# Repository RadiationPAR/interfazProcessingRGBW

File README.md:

# PowerPAR-Led DELMA
---
La formulación de un problema es a menudo más esencial que su solución, que puede ser meramente una materia de destreza experimental o matemática. "La especificación del problema a investigar implica que se ha comprendido plenamente el
tema de la investigación, hasta el punto de poder determinar exactamente los interrogantes principales que plantea y a cuya resolución se debe orientar la investigación." Einstein

## SISTEMA DE MEDICIÓN Y MONITOREO PARA EL ESTUDIO DEL EFECTO DE LA RADIACIÓN PAR EN LAS PLANTAS

Esta investigación discrimina la información científica y tecnológica experimental a la fecha sobre la Radiación Fotosintéticamente Activa (radiación integrada del rango de longitudes de onda que son capaces de producir actividad fotosintética en las plantas y otros organismos fotosintéticos como microalgas y bacterias).

Investigadores de todo el planeta exponen en sus artículos que los vegetales necesitan porciones de luz desde los 400nm hasta los 700 nm; conocer sus umbrales luminicos permitirá conseguir cosechas de gran producción y alta calidad; llevar un historial de datos sobre el efecto de la longitud de onda según las horas del día y los estadios de crecimiento de la planta permitirá a futuro disponer de hojas de datos para realizar agricultura de precisión en su parametro luminico. 

A continuación se plantea el desarrollo de un mecanismo de observación para la respuesta fisiológica del dosel vegetal (en especial de la fotosíntesis), a partir del diseño de un sistema de iluminación artificial basado en un estudio previo de sistemas de iluminación y la actual migración a sistemas de iluminación con tecnología LED y OLED cuyo espectro de radiación esta dado en una banda especifica lo que proporciona un menor gasto de potencia, y facilita irradiar la planta con la parte del espectro especifico que ella necesita según su estadio: germinación, vegetación y floración. 

Fabricantes de todo el mundo, ofrecen al mercado diversas lamparas de iluminación y en algunos casos se diseñan enormes arreglos de leds con iluminación fija o invariable garantizando solo su uso para determinado tipo de plantas (C3, C4, CAM) - plantas presentes en la industria hortícola de mayor producción. Los investigadores de diversas tesis de Maestría y Doctorado no realizan un proceso fiable para llevar la trazabilidad de sus datos pero nos ilustran sobre el metodo científico iterado para obtener mejoras en el proceso de crecimiento y floración de diversas genéticas de plantas.  

Esta investigación contempla el desarrollo de un prototipo que permite al usuario manejar: la composición de color (longitud de onda) a irradiar y su potencia a traves de una interfaz de fácil manejo que almacena datos de manera centralizada como lo son: composición RGB (0-255), composición CMY (0 - 255), Matiz (0 - 360), saturación (0.0 - 1.0), luminancia (0.0 - 1.0), posición XYZ del color, longitud de onda y frecuencia.   

# Materiales
---  
## Microcontrolador Tiva C Series  
Se decide implementar este microcontrolador por su fama en internet acerca de la adquisición, procesamiento y almacenamiento de datos; ademas se sirve de una librería para la compresión de algoritmos matemáticos, lo cual resulta bastante interesante y acorde para las conversiones de los diferentes modelos matemáticos de los espacios del color.

## Sensor TCS3220 y Led RGB 100W
Se opta por implementar el sensor TCS3220 por su resolución y economía; basicamente entrega una señal cuadrada con ancho de pulso variable de acuerdo a la presencia de una fuente de luz. Se caracteriza el comportamiento del sensor con la hoja de datos del fabricante y datos de pruebas en el laboratorio de ensayos eléctricos de la Universidad Nacional - LABE.  

El led de 100W permite dimensionar espacios de manera modular y cumple con los requisitos mínimos de lumenes para estimular la fotosíntesis en plantas C3, C4 y CAM.

# Diseño esquematico y PCB 
---  
## Circuito de Potencia

## Circuito de Control

---  

# Interfaz de Control con Processing desde una Raspberry

Para el desarrollo de la interfaz se usa el software libre Processing - ampliamente usado para comunicación entre el usuario y la maquina por el protocolo RS-232 haciendo el llamado de la libreria "ControlP5".  
Para configurarle en una **raspberry** deben ejecutarse los siguientes comandos: 
<pre><code>cd interfazProcessingRGBW/PROCESSING/controlP5-2.2.5/controlP5/library</code></pre>
<pre><code>cp controlP5.jar /usr/local/lib/processing-3.2.3/core/library</code></pre>  
---

## Investigador principal
* Diego Javier Mena - Email: ingelectronicadj@gmail.com

## Apoyo a la investigación

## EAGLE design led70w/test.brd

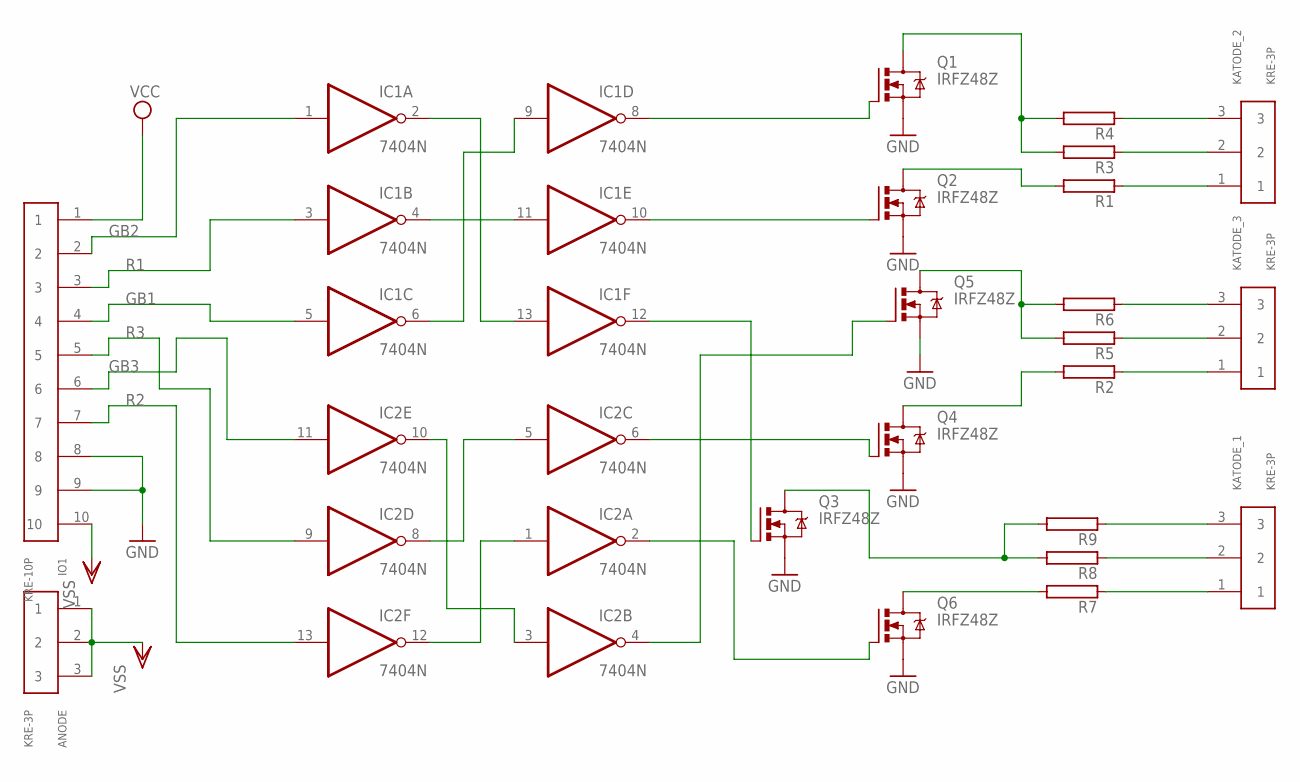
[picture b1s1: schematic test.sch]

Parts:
ANODE: KRE-3P
IC1, IC2: 7404N; DIL14
IO1: KRE-10P
KATODE_1, KATODE_2, KATODE_3: KRE-3P
Q1, Q2, Q3, Q4, Q5, Q6: IRFZ48Z; TO220BH
R1, R2, R3, R4, R5, R6, R7, R8, R9: RAC10; AC10

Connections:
GB1: IC1.5 (I), IO1.4
GB2: IC1.1 (I), IO1.2
GB3: IC2.11 (I), IO1.6
GND: IC1.7 (GND), IC2.7 (GND), IO1.8, IO1.9, Q1.S, Q2.S, Q3.S, Q4.S, Q5.S, Q6.S
K_B: Q2.D, R1.2
K_B2: Q5.D, R5.2, R6.2
K_R: Q1.D, R3.2, R4.2
unnamed: IC1.8 (O), Q1.G
unnamed: IC1.10 (O), Q2.G
unnamed: KATODE_2.1, R1.1
unnamed: IC1.12 (O), Q3.G
unnamed: IC1.4 (O), IC1.11 (I)
unnamed: IC2.1 (I), IC2.12 (O)
unnamed: IC2.5 (I), IC2.8 (O)
unnamed: IC2.6 (O), Q4.G
unnamed: IC2.2 (O), Q6.G
unnamed: IC2.4 (O), Q5.G
unnamed: IC2.3 (I), IC2.10 (O)
unnamed: IC1.6 (O), IC1.9 (I)
unnamed: KATODE_2.2, R3.1
unnamed: KATODE_2.3, R4.1
unnamed: IC1.2 (O), IC1.13 (I)
unnamed: KATODE_3.1, R2.1
unnamed: KATODE_3.2, R5.1
unnamed: KATODE_3.3, R6.1
unnamed: KATODE_1.1, R7.1
unnamed: KATODE_1.2, R8.1
unnamed: KATODE_1.3, R9.1
unnamed: Q3.D, R8.2, R9.2
unnamed: Q6.D, R7.2
unnamed: Q4.D, R2.2
R1: IC1.3 (I), IO1.3
R2: IC2.13 (I), IO1.7
R3: IC2.9 (I), IO1.5
VCC: IC1.14 (VCC), IC2.14 (VCC), IO1.1
VSS: ANODE.1, ANODE.2, ANODE.3, IO1.10

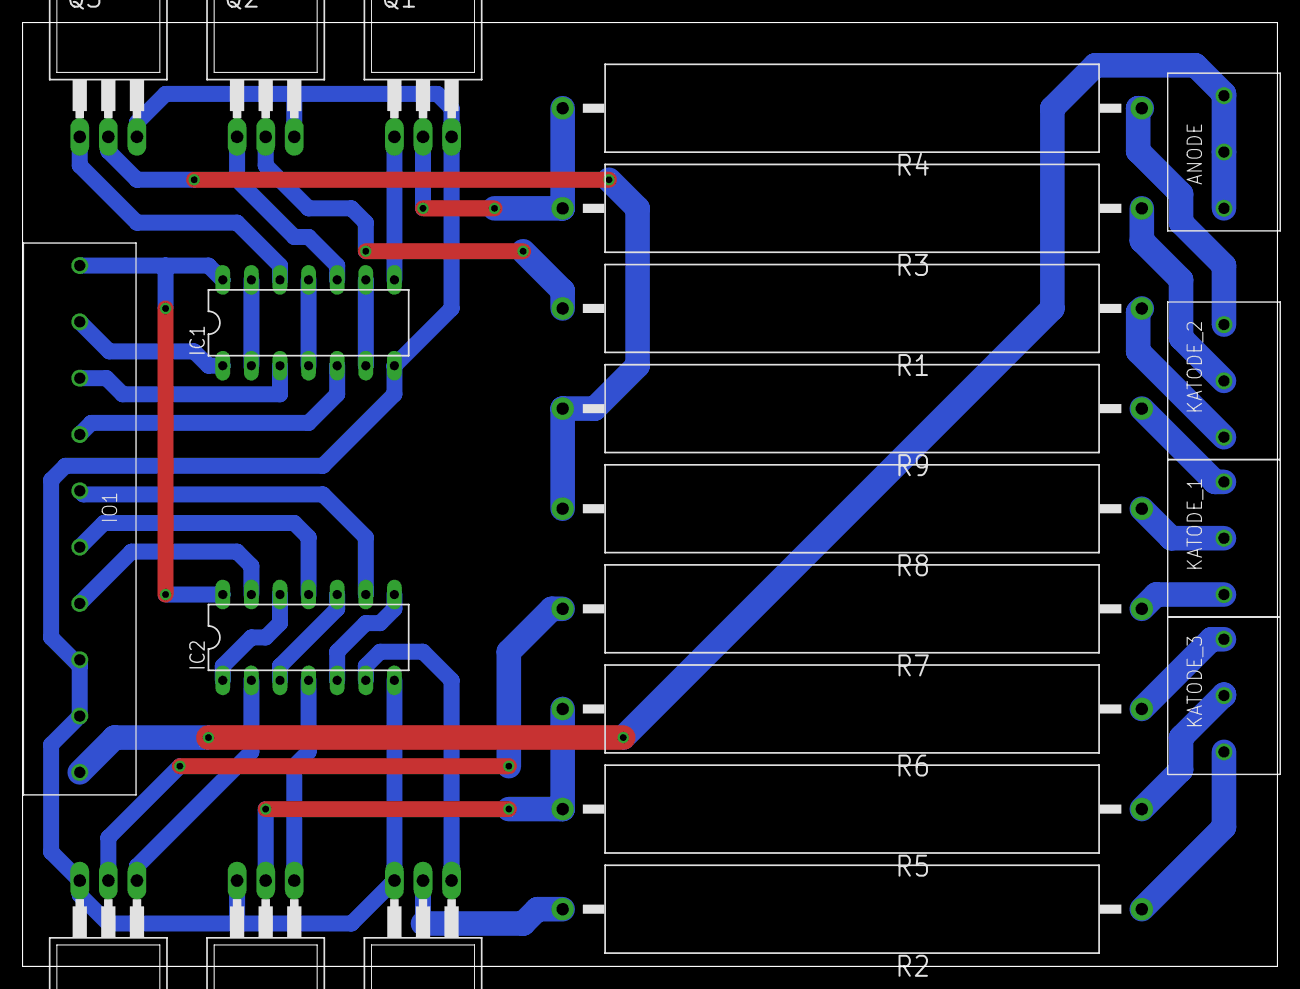
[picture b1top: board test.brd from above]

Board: 2 copper layers, 111.4 x 83.8 mm, 22 parts (0 on the bottom side), 36 nets.

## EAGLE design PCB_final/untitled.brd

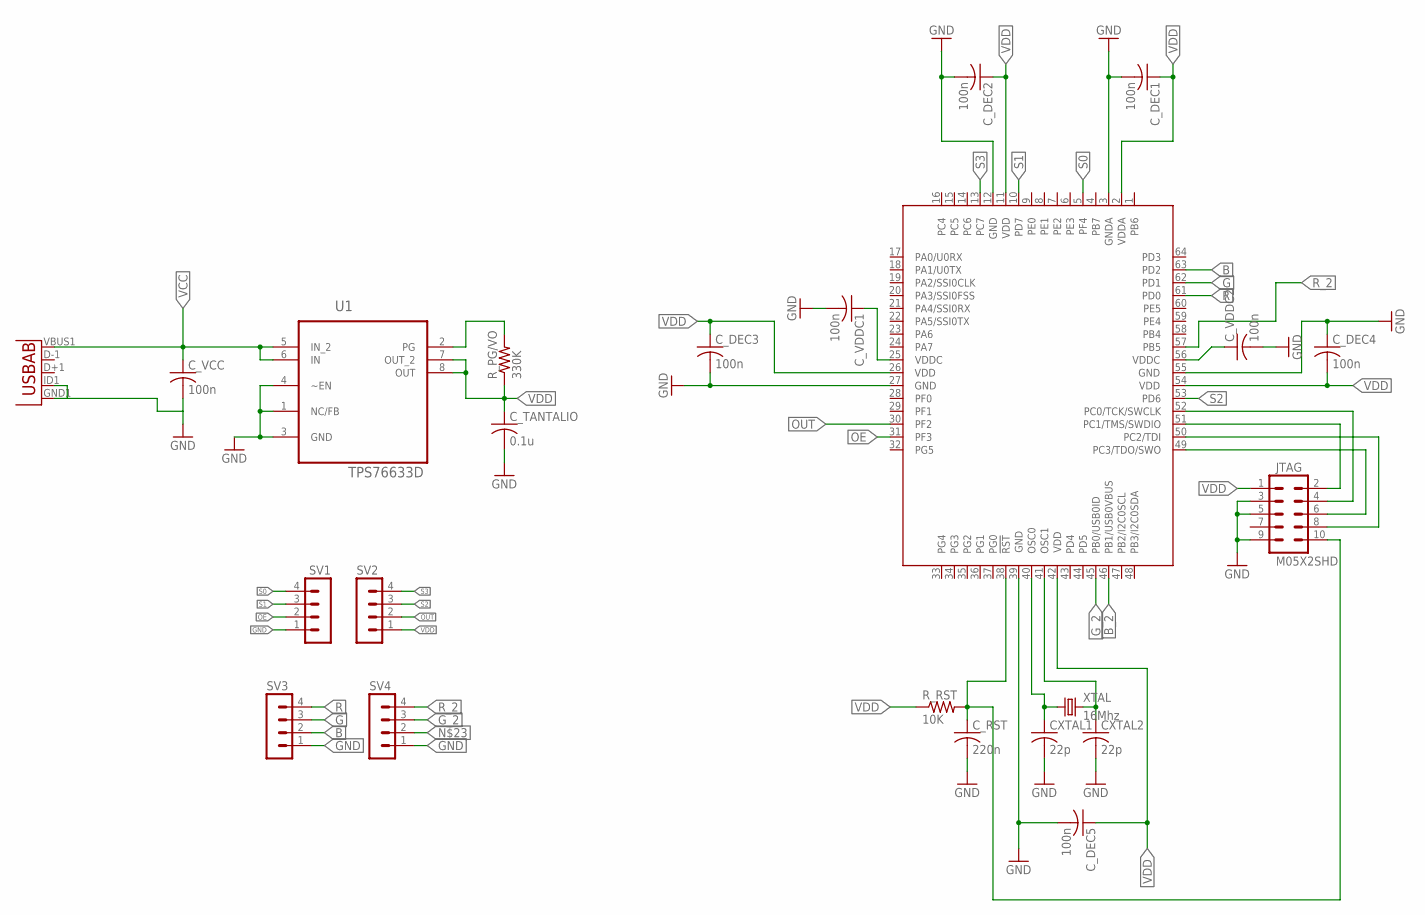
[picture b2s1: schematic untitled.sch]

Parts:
CXTAL1, CXTAL2: 22p; C0805
C_DEC1, C_DEC2, C_DEC3, C_DEC4, C_DEC5: 100n; C0805
C_RST: 220n; C0805
C_TANTALIO: 0.1u; C1206
C_VCC: 100n; C0805
C_VDDC1, C_VDDC2: 100n; C0805
JTAG: M05X2SHD; 2X5-SHROUDED
R_PG/VO: 330K; M1206
R_RST: 10K; M1206
SV1, SV2, SV3, SV4: MA04-1
TM4C123FH6PM: TM4C123[6,F]XXPM; PM_S-PQFP-G64
U1: TPS76633D; SOIC127P600X175-8N
U3: USB""; USB-MICRO-SMD
XTAL: 16Mhz; HC49UP

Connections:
B: SV3.2, TM4C123FH6PM.63 (PD2)
B_2: TM4C123FH6PM.46 (PB1/USB0VBUS)
G: SV3.3, TM4C123FH6PM.62 (PD1)
GND: CXTAL1.2, CXTAL2.2, C_DEC1.2, C_DEC2.2, C_DEC3.2, C_DEC4.1, C_DEC5.2, C_RST.2, C_TANTALIO.2, C_VCC.2, C_VDDC1.2, C_VDDC2.2, JTAG.3, JTAG.5, JTAG.9, SV1.1, SV3.1, SV4.1, TM4C123FH6PM.3 (GNDA), TM4C123FH6PM.12 (GND), TM4C123FH6PM.27 (GND), TM4C123FH6PM.39 (GND), TM4C123FH6PM.55 (GND), U1.1 (NC/FB), U1.3 (GND), U1.4 (~EN), U3.GND1 (GND), U3.ID1 (USBID)
G_2: SV4.3, TM4C123FH6PM.45 (PB0/USB0ID)
unnamed: CXTAL1.1, TM4C123FH6PM.40 (OSC0), XTAL.1
unnamed: CXTAL2.1, TM4C123FH6PM.41 (OSC1), XTAL.2
unnamed: C_VDDC1.1, TM4C123FH6PM.25 (VDDC)
unnamed: JTAG.2, TM4C123FH6PM.51 (PC1/TMS/SWDIO)
unnamed: JTAG.4, TM4C123FH6PM.52 (PC0/TCK/SWCLK)
unnamed: C_VDDC2.1, TM4C123FH6PM.56 (VDDC)
unnamed: JTAG.6, TM4C123FH6PM.49 (PC3/TDO/SWO)
unnamed: R_PG/VO.2, U1.2 (PG)
unnamed: JTAG.8, TM4C123FH6PM.50 (PC2/TDI)
unnamed: C_RST.1, JTAG.10, R_RST.2, TM4C123FH6PM.38 (!RST)
OE: SV1.2, TM4C123FH6PM.31 (PF3)
OUT: SV2.2, TM4C123FH6PM.30 (PF2)
R: SV3.4, TM4C123FH6PM.61 (PD0)
R_2: SV4.4, TM4C123FH6PM.57 (PB5)
S0: SV1.4, TM4C123FH6PM.5 (PF4)
S1: SV1.3, TM4C123FH6PM.10 (PD7)
S2: SV2.3, TM4C123FH6PM.53 (PD6)
S3: SV2.4, TM4C123FH6PM.13 (PC7)
VCC: C_VCC.1, U1.5 (IN_2), U1.6 (IN), U3.VBUS1 (VBUS)
VDD: C_DEC1.1, C_DEC2.1, C_DEC3.1, C_DEC4.2, C_DEC5.1, C_TANTALIO.1, JTAG.1, R_PG/VO.1, R_RST.1, SV2.1, TM4C123FH6PM.2 (VDDA), TM4C123FH6PM.11 (VDD), TM4C123FH6PM.26 (VDD), TM4C123FH6PM.42 (VDD), TM4C123FH6PM.54 (VDD), U1.7 (OUT_2), U1.8 (OUT)

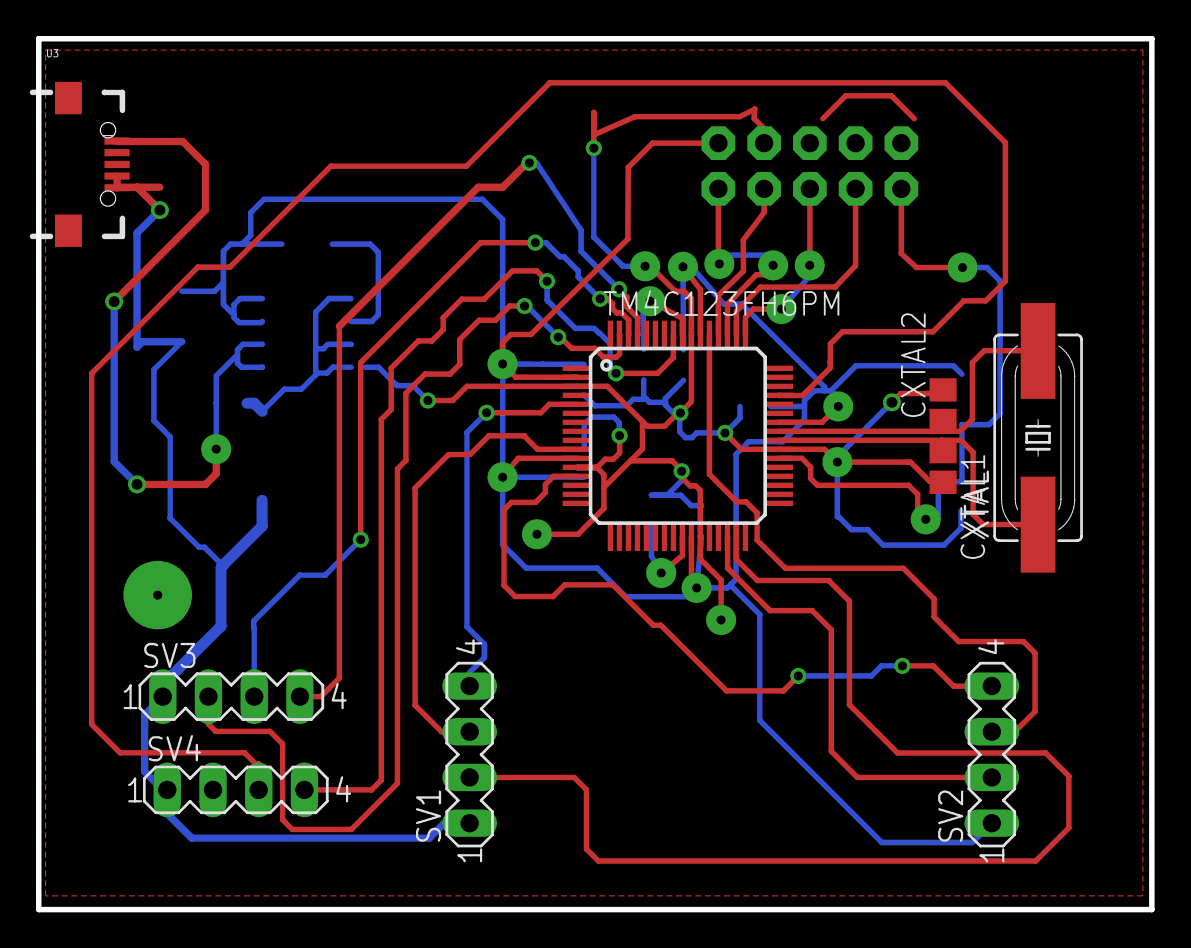
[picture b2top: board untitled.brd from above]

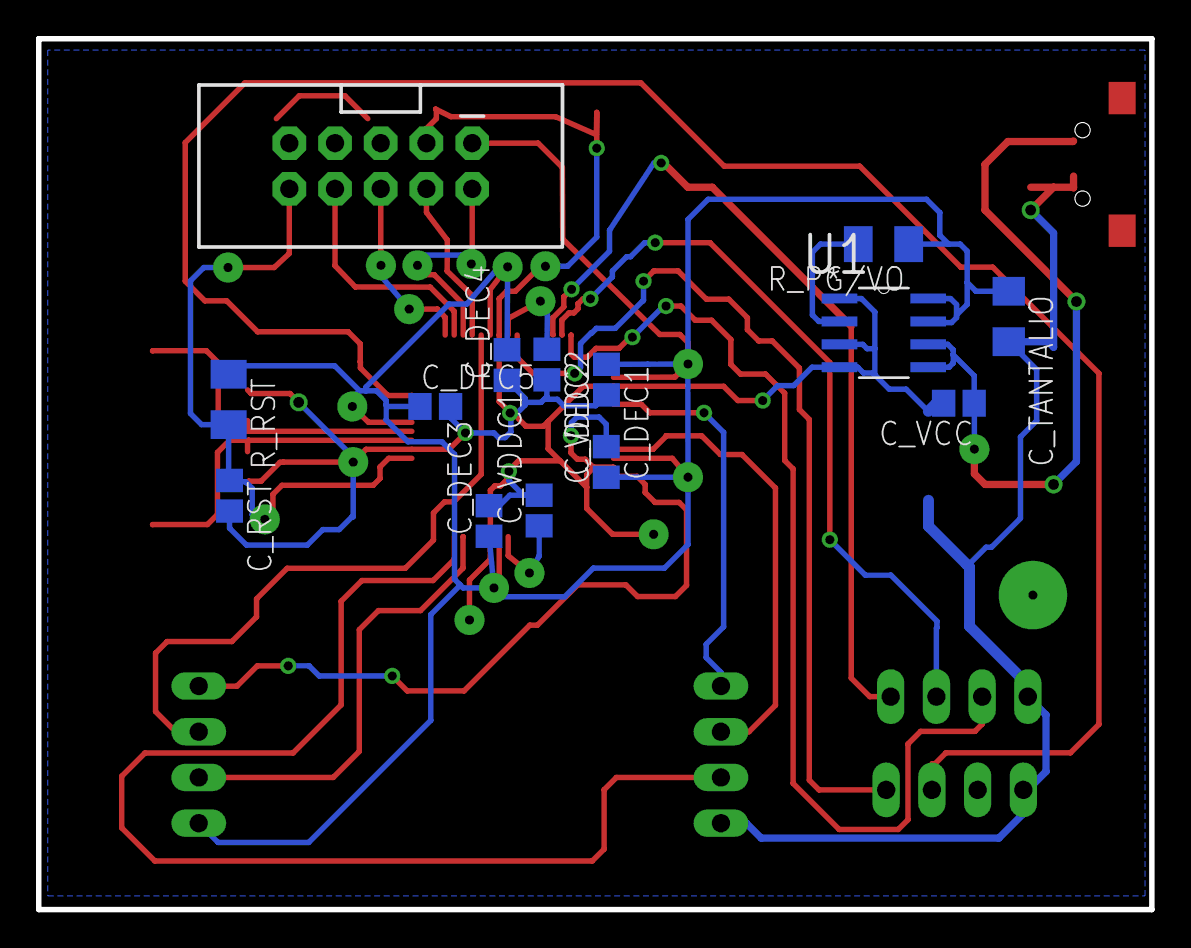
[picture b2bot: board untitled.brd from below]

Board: 2 copper layers, 61.8 x 48.4 mm, 23 parts (14 on the bottom side), 24 nets.

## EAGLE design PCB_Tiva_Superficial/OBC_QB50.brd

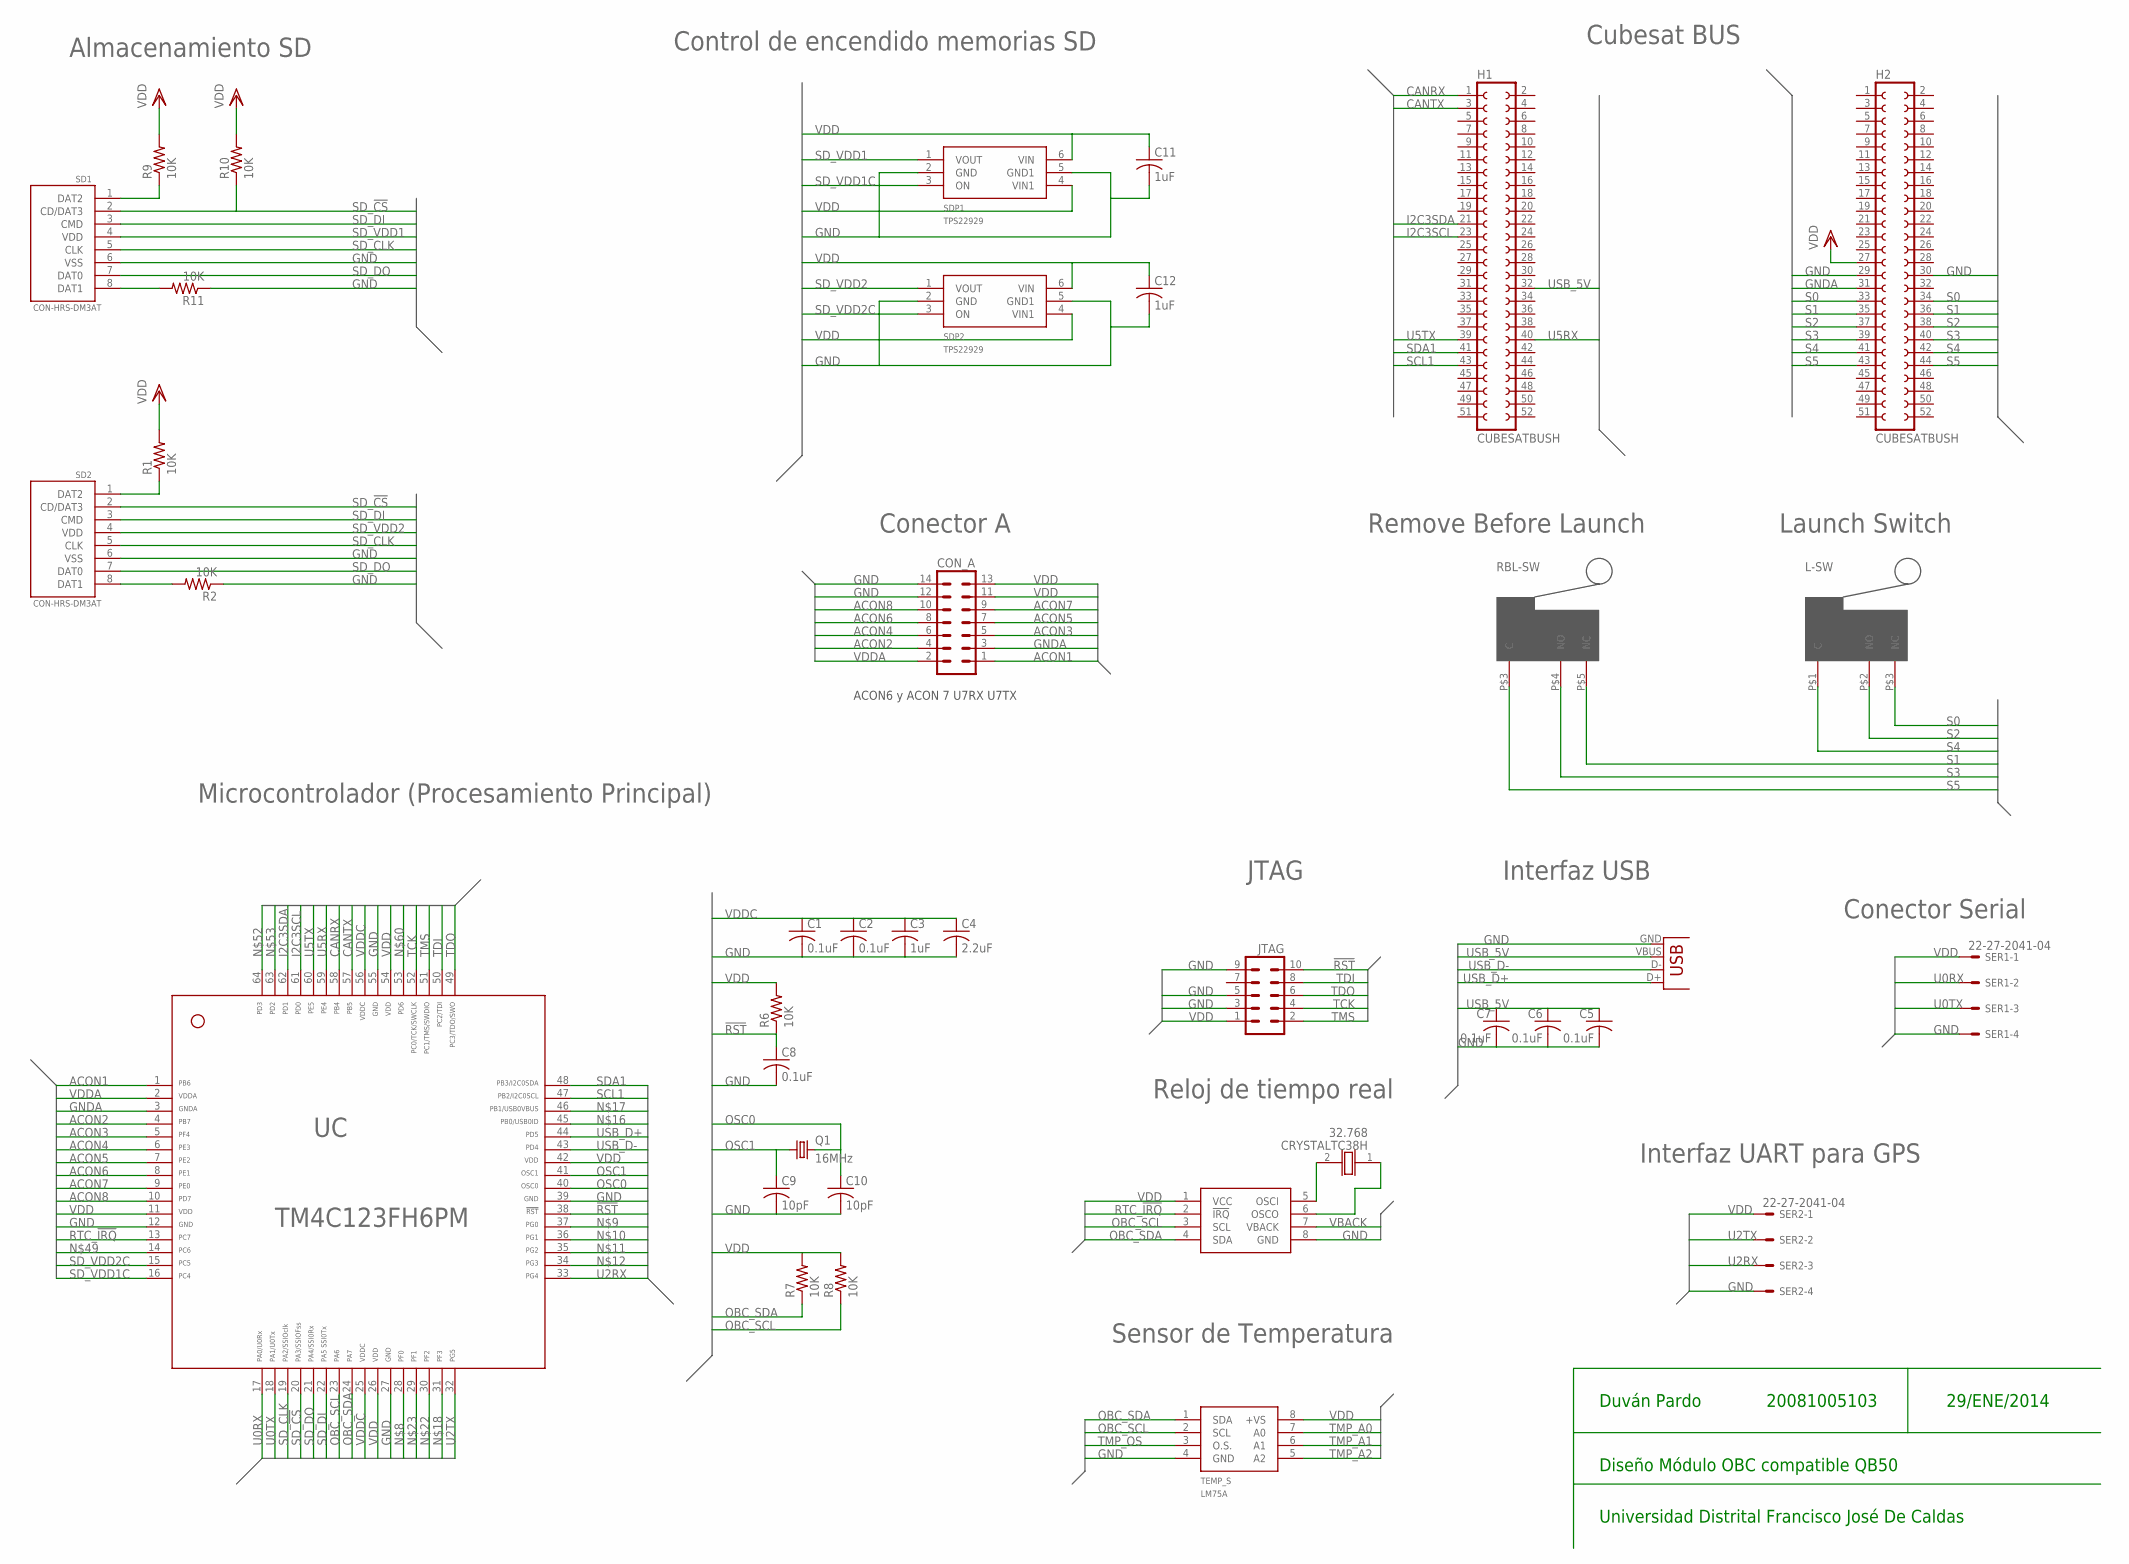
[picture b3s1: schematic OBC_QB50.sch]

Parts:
32.768: CRYSTALTC38H; TC38H
C1, C2, C5, C6, C7, C8: 0.1uF; C0402
C3, C11, C12: 1uF; C0402
C4: 2.2uF; C0402
C9, C10: 10pF; C0402
CON_A: ML14
H1, H2: CUBESATBUSH; CUBESATBUS
JTAG: ML10
L-SW: SW_E61-SERIESCON; CON
Q1: 16MHz; HC49UP
R1, R2, R6, R7, R8, R9, R10, R11: 10K; MINI_MELF-0102R
RBL-SW: SW_E61-SERIES; E61-SERIES
RTC: BQ32008SOIC; SOP08
SD1, SD2: CON-HRS-DM3AT; HRS-DM3AT
SDP1, SDP2: TPS22929; SOT23-6L
SER1, SER2: 22-27-2041-04; 6410-04
TEMP_S: LM75A; SOP08
UC: TM4C123FH6PM
USB: USB-B-H

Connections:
!RST: C8.1, JTAG.10, R6.1, UC.38
ACON1: CON_A.1, UC.1
ACON2: CON_A.4, UC.4
ACON3: CON_A.5, UC.5
ACON4: CON_A.6, UC.6
ACON5: CON_A.7, UC.7
ACON6: CON_A.8, UC.8
ACON7: CON_A.9, UC.9
ACON8: CON_A.10, UC.10
CANRX: H1.1, UC.58
CANTX: H1.3, UC.57
GND: C1.2, C2.2, C3.2, C4.2, C5.2, C6.2, C7.2, C8.2, C9.2, C10.2, C11.2, C12.2, CON_A.12, CON_A.14, H2.29, H2.30, JTAG.3, JTAG.5, JTAG.9, R2.1, R11.1, RTC.8 (GND), SD1.6 (VSS), SD2.6 (VSS), SDP1.2 (GND), SDP1.5 (GND1), SDP2.2 (GND), SDP2.5 (GND1), SER1.4, SER2.4, TEMP_S.4 (GND), UC.12, UC.27, UC.39, UC.55, USB.GND
GNDA: CON_A.3, H2.31, UC.3
I2C3SCL: H1.23, UC.61
I2C3SDA: H1.21, UC.62
unnamed: R1.1, SD2.1 (DAT2)
unnamed: R2.2, SD2.8 (DAT1)
unnamed: 32.768.2 (X2), RTC.5 (OSCI)
unnamed: 32.768.1 (X1), RTC.6 (OSCO)
unnamed: R9.1, SD1.1 (DAT2)
unnamed: R11.2, SD1.8 (DAT1)
OBC_SCL: R8.1, RTC.3 (SCL), TEMP_S.2 (SCL), UC.23
OBC_SDA: R7.1, RTC.4 (SDA), TEMP_S.1 (SDA), UC.24
OSC0: C10.1, Q1.2, UC.40
OSC1: C9.1, Q1.1, UC.41
RTC_!IRQ: RTC.2 (!IRQ), UC.13
S0: H2.33, H2.34, L-SW.P$3 (NC)
S1: H2.35, H2.36, RBL-SW.P$5 (NC)
S2: H2.37, H2.38, L-SW.P$2 (NO)
S3: H2.39, H2.40, RBL-SW.P$4 (NO)
S4: H2.41, H2.42, L-SW.P$1 (C)
S5: H2.43, H2.44, RBL-SW.P$3 (C)
SCL1: H1.43, UC.47
SDA1: H1.41, UC.48
SD_!CS: R10.1, SD1.2 (CD/DAT3), SD2.2 (CD/DAT3), UC.20
SD_CLK: SD1.5 (CLK), SD2.5 (CLK), UC.19
SD_DI: SD1.3 (CMD), SD2.3 (CMD), UC.22
SD_DO: SD1.7 (DAT0), SD2.7 (DAT0), UC.21
SD_VDD1: SD1.4 (VDD), SDP1.1 (VOUT)
SD_VDD1C: SDP1.3 (ON), UC.16
SD_VDD2: SD2.4 (VDD), SDP2.1 (VOUT)
SD_VDD2C: SDP2.3 (ON), UC.15
TCK: JTAG.4, UC.52
TDI: JTAG.8, UC.50
TDO: JTAG.6, UC.49
TMP_A0: TEMP_S.7 (A0)
TMP_A1: TEMP_S.6 (A1)
TMP_A2: TEMP_S.5 (A2)
TMP_OS: TEMP_S.3 (O.S.)
TMS: JTAG.2, UC.51
U0RX: SER1.2, UC.17
U0TX: SER1.3, UC.18
U2RX: SER2.3, UC.33
U2TX: SER2.2, UC.32
U5RX: H1.40, UC.59
U5TX: H1.39, UC.60
USB_5V: C5.1, C6.1, C7.1, H1.32, USB.VBUS
USB_D+: UC.44, USB.D+
USB_D-: UC.43, USB.D-
VBACK: RTC.7 (VBACK)
VDD: C11.1, C12.1, CON_A.11, CON_A.13, H2.27, JTAG.1, R1.2, R6.2, R7.2, R8.2, R9.2, R10.2, RTC.1 (VCC), SDP1.4 (VIN1), SDP1.6 (VIN), SDP2.4 (VIN1), SDP2.6 (VIN), SER1.1, SER2.1, TEMP_S.8 (+VS), UC.11, UC.26, UC.42, UC.54
VDDA: CON_A.2, UC.2
VDDC: C1.1, C2.1, C3.1, C4.1, UC.25, UC.56

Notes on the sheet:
Almacenamiento SD
Cubesat BUS
JTAG
Microcontrolador (Procesamiento Principal)
Interfaz USB
Remove Before Launch
Launch Switch
Reloj de tiempo real
Control de encendido memorias SD
Conector A
Conector Serial
Duván Pardo
Universidad Distrital Francisco José De Caldas
Diseño Módulo OBC compatible QB50
29/ENE/2014
20081005103
Sensor de Temperatura
ACON6 y ACON 7 U7RX U7TX
Interfaz UART para GPS

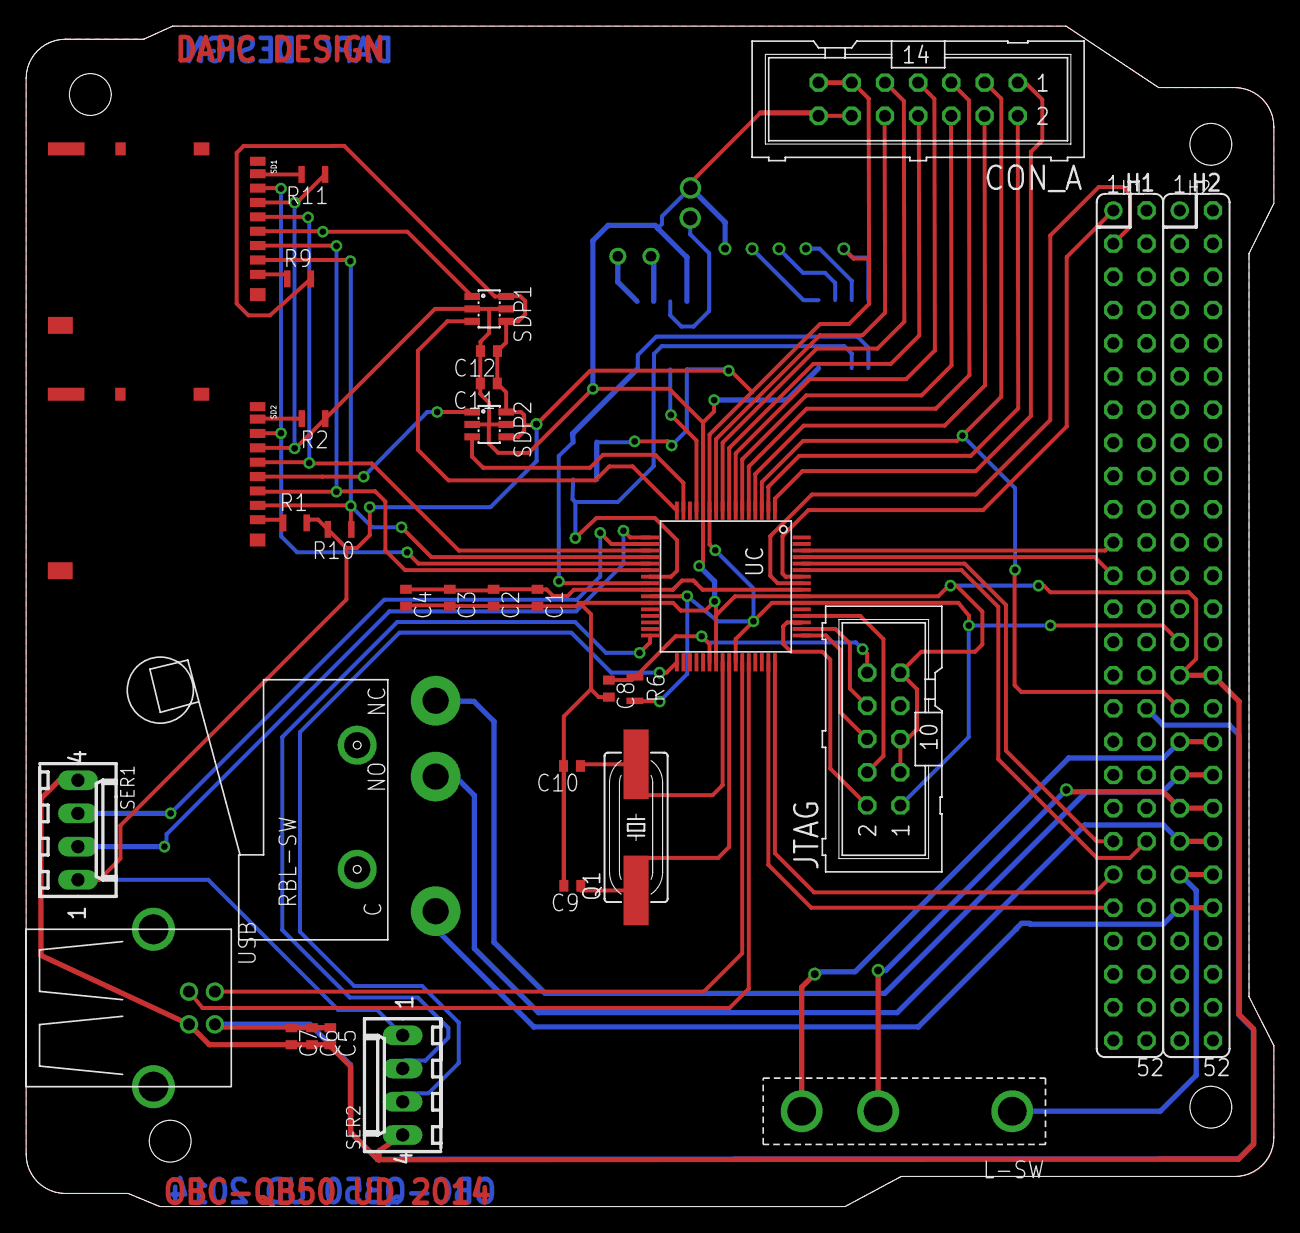
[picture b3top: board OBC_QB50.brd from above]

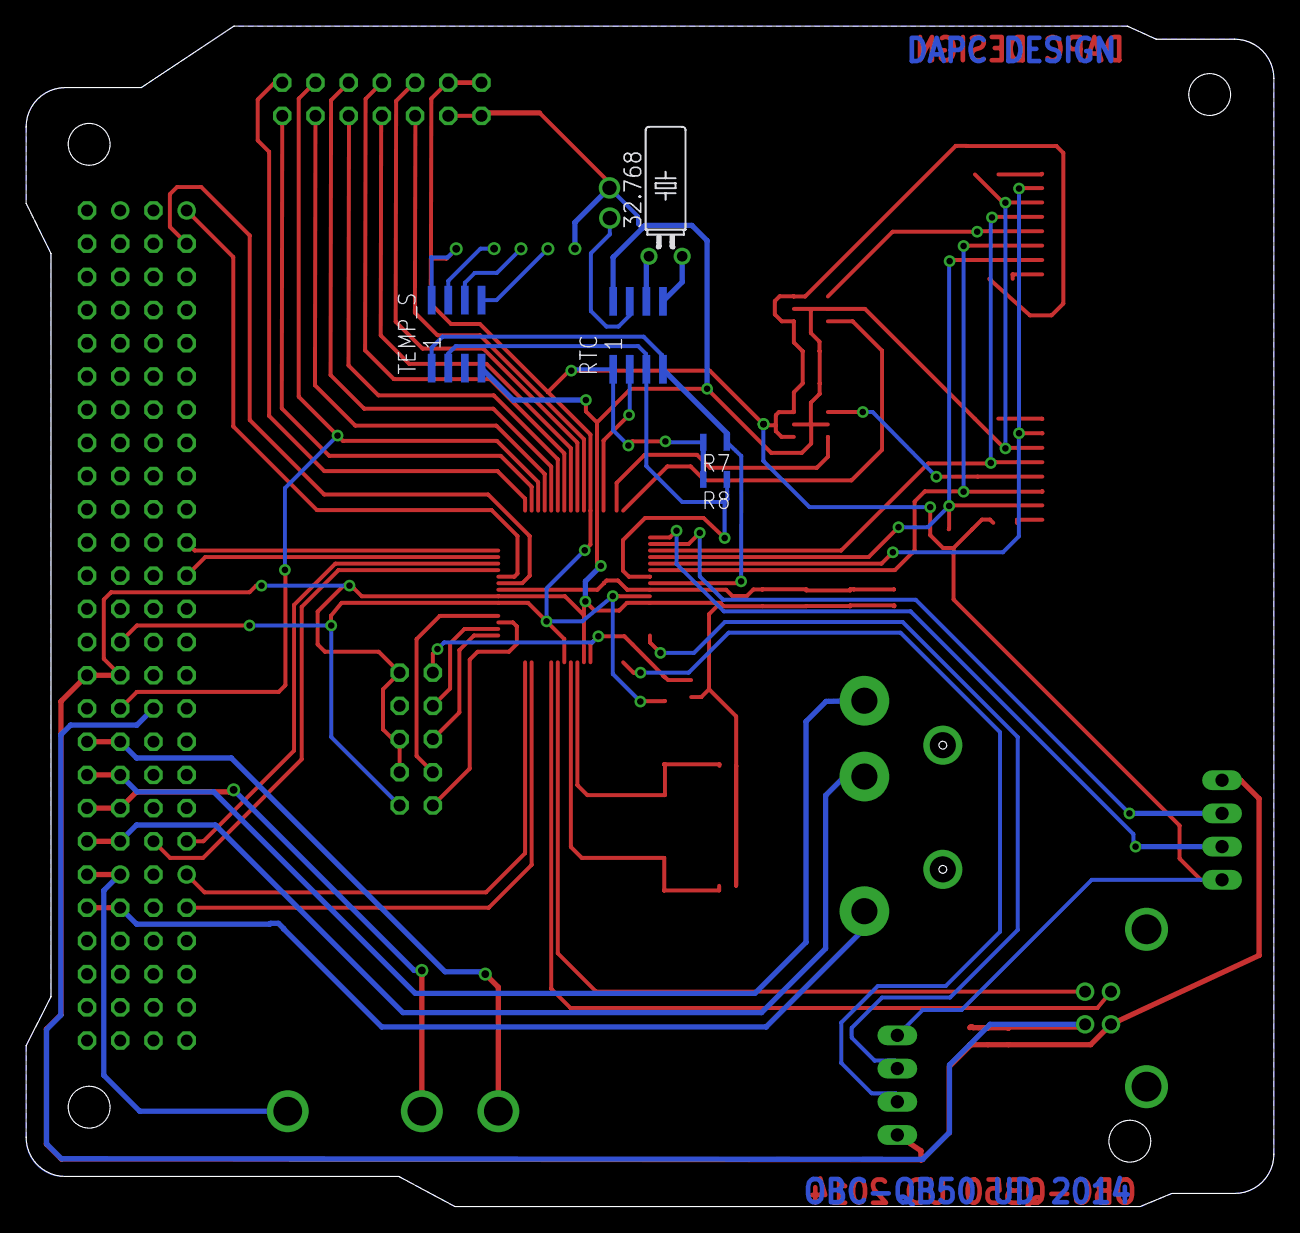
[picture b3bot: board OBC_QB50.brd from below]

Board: 4 copper layers, 95.5 x 90.3 mm, 38 parts (5 on the bottom side), 58 nets.

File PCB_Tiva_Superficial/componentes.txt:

Partlist exported from /home/asus/ganttproject/interfazProcessingRGBW/PCB_Tiva_Superficial/OBC_QB50.sch at 29/01/17 12:49

Part   Value         Device           Package         Description                         DIGI-KEY#   MF     MPN            OC_FARNELL OC_NEWARK TERMINATION-TYPE          
32.768 CRYSTALTC38H  CRYSTALTC38H     TC38H           Generic Crystal TC38H 32.768                                                                                         
C1     0.1uF         C-USC0402        C0402           CAPACITOR, American symbol                                                                                           
C2     0.1uF         C-USC0402        C0402           CAPACITOR, American symbol                                                                                           
C3     1uF           C-USC0402        C0402           CAPACITOR, American symbol                                                                                           
C4     2.2uF         C-USC0402        C0402           CAPACITOR, American symbol                                                                                           
C5     0.1uF         C-USC0402        C0402           CAPACITOR, American symbol                                                                                           
C6     0.1uF         C-USC0402        C0402           CAPACITOR, American symbol                                                                                           
C7     0.1uF         C-USC0402        C0402           CAPACITOR, American symbol                                                                                           
C8     0.1uF         C-USC0402        C0402           CAPACITOR, American symbol                                                                                           
C9     10pF          C-USC0402        C0402           CAPACITOR, American symbol                                                                                           
C10    10pF          C-USC0402        C0402           CAPACITOR, American symbol                                                                                           
C11    1uF           C-USC0402        C0402           CAPACITOR, American symbol                                                                                           
C12    1uF           C-USC0402        C0402           CAPACITOR, American symbol                                                                                           
CON_A                ML14             ML14            HARTING                                                               unknown    unknown                             
H1     CUBESATBUSH   CUBESATBUSH      CUBESATBUS                                                                                                                           
H2     CUBESATBUSH   CUBESATBUSH      CUBESATBUS                                                                                                                           
JTAG                 ML10             ML10            HARTING                                                               unknown    unknown                             
L-SW                 SW_E61-SERIESCON CON             SW-E61-SERIES                                                                                                        
Q1     16MHz         CRYSTALHC49UP    HC49UP          CRYSTAL                                                               unknown    unknown                             
R1     10K           R-US_MELF0102R   MINI_MELF-0102R RESISTOR, American symbol                                                                                            
R2     10K           R-US_MELF0102R   MINI_MELF-0102R RESISTOR, American symbol                                                                                            
R6     10K           R-US_MELF0102R   MINI_MELF-0102R RESISTOR, American symbol                                                                                            
R7     10K           R-US_MELF0102R   MINI_MELF-0102R RESISTOR, American symbol                                                                                            
R8     10K           R-US_MELF0102R   MINI_MELF-0102R RESISTOR, American symbol                                                                                            
R9     10K           R-US_MELF0102R   MINI_MELF-0102R RESISTOR, American symbol                                                                                            
R10    10K           R-US_MELF0102R   MINI_MELF-0102R RESISTOR, American symbol                                                                                            
R11    10K           R-US_MELF0102R   MINI_MELF-0102R RESISTOR, American symbol                                                                                            
RBL-SW               SW_E61-SERIES    E61-SERIES      SW-E61-SERIES                                                                                                        
RTC    BQ32008SOIC   BQ32008SOIC      SOP08                                                                                                                                
SD1    CON-HRS-DM3AT CON-HRS-DM3AT    HRS-DM3AT       Hirose DM3AT microSD card connector HR1964CT-ND Hirose DM3AT-SF-PEJM5                      Right-angle SMT (standard)
SD2    CON-HRS-DM3AT CON-HRS-DM3AT    HRS-DM3AT       Hirose DM3AT microSD card connector HR1964CT-ND Hirose DM3AT-SF-PEJM5                      Right-angle SMT (standard)
SDP1   TPS22929      TPS22929         SOT23-6L        Description                                                                                                          
SDP2   TPS22929      TPS22929         SOT23-6L        Description                                                                                                          
SER1   22-27-2041-04 22-27-2041-04    6410-04         CONNECTOR                                                             unknown    unknown                             
SER2   22-27-2041-04 22-27-2041-04    6410-04         CONNECTOR                                                             unknown    unknown                             
TEMP_S LM75A         LM75A            SOP08                                                                                                                                
UC     TM4C123FH6PM  TM4C123FH6PM     TM4C123FH6PM    TM4C123FH6PM                                                                                                         
USB    USB-B-H       USB-B-H          USB-B-H         USB Connectors

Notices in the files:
parts and their libraries:
SparkFun-Connectors: Licensing: Creative Commons ShareAlike 4.0 International - https://creativecommons.org/licenses/by-sa/4.0
